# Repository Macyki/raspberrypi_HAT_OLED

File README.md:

# raspberrypi_HAT_OLED
# raspberrypi_HAT_OLED
# raspberrypi_HAT_OLED
# raspberrypi_HAT_OLED

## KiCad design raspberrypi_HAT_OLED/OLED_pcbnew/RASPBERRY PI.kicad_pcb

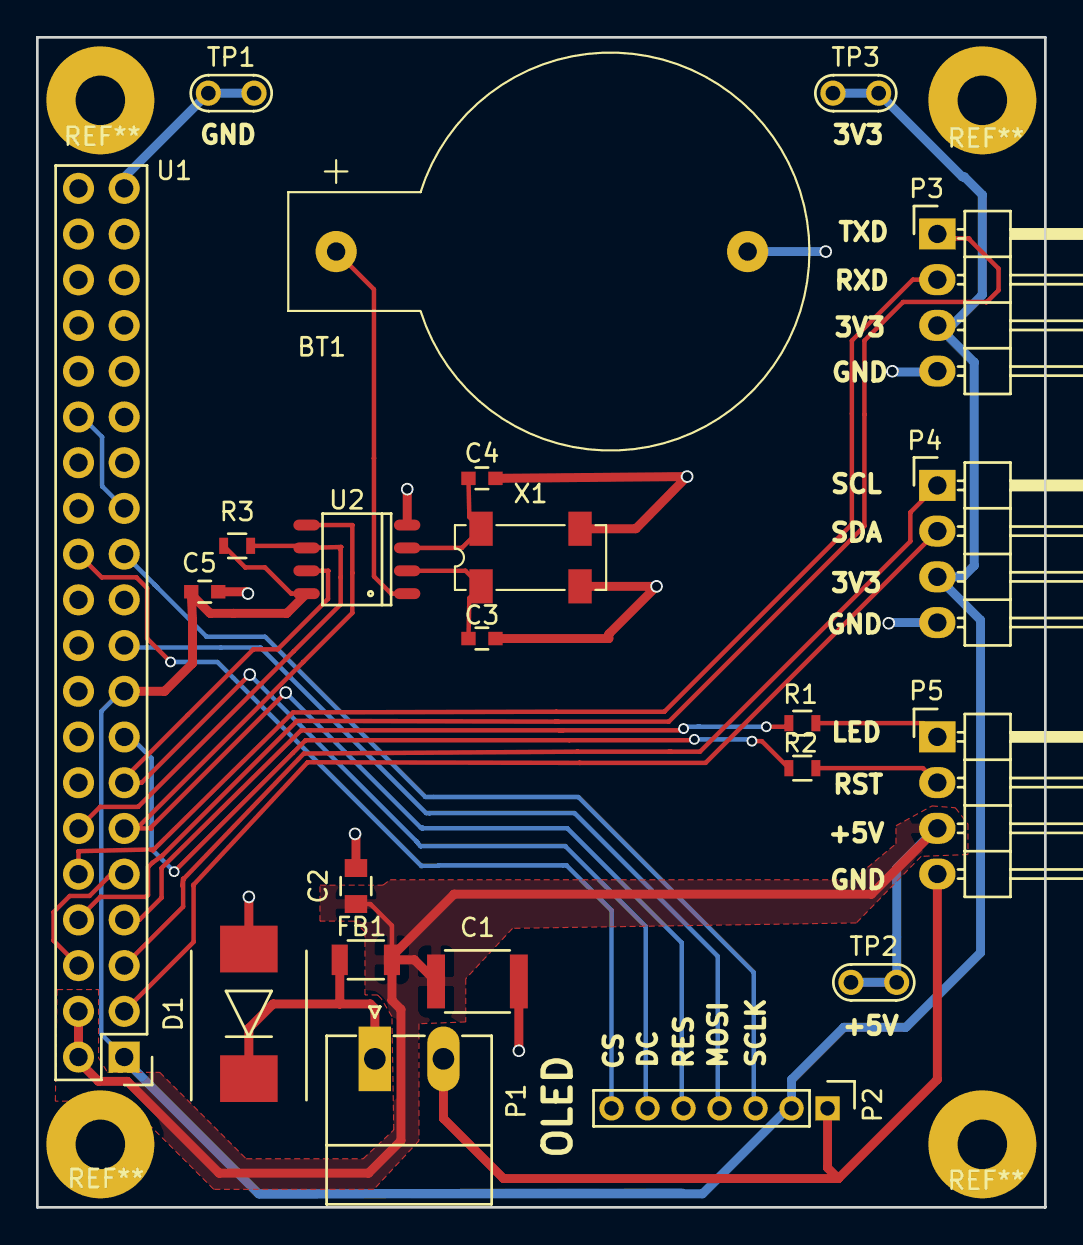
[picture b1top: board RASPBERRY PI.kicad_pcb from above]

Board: 2 copper layers, 56.0 x 65.0 mm, 22 parts (0 on the bottom side), 21 nets.

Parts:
BT1: CR1220-3V; CR2032H
C1: 47uF/10V/TAN; C_1812
C2: 2.2uF; C_0805
C3, C4: 10pF; C_0603
C5: 0.1uF; C_0603
D1: SAA5.0; DO-214AB
FB1: CIZHU_121R/6A; R_1206
P1: XH3.81-2P; PhoenixContact_MC-G_02x3.81mm_Angled
P2: XH2.0-7P; Pin_Header_Straight_1x07_Pitch2.00mm
P3, P4, P5: XH2.54-4P; Pin_Header_Angled_1x04
R1, R2: 330; R_0603
R3: 10K; R_0603
TP1, TP2, TP3: TESTPOINT; Test_Point
U1: Raspberry_Pi_B+; Pin_Header_Straight_2x20
U2: DS1302; SO-8
X1: E1WSDA12-32.768KHZ; Crystal_SMD_SeikoEpson_MC306-4pin_8.0x3.2mm

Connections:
+3V3: C5.1, P2.2, P3.3, P4.3, R3.1, TP3.1, U1.1, U1.17, U2.8
+5V: C1.1, C2.1, FB1.2, P5.3, TP2.1, U1.2, U1.4
/RTC_CE: P2.5, U1.11, U2.5
/RTC_IO: R3.2, U1.12, U2.6
/RTC_SCLK: P2.6, U1.13, U2.7
/SPI_CS: P2.7, U1.24
/SPI_MOSI: P2.4, U1.19
/SPI_SCLK: P2.3, U1.23
GND: BT1.2, C1.2, C2.2, C3.2, C4.2, C5.2, D1.2, P1.2, P2.1, P3.4, P4.4, P5.4, TP1.1, U1.6, U1.9, U1.14, U1.20, U1.25, U1.30, U1.34, U1.39, U2.4, X1.2, X1.3
unnamed: BT1.1, U2.1
unnamed: C3.1, U2.2, X1.1
unnamed: C4.1, U2.3, X1.4
unnamed: D1.1, FB1.1, P1.1
unnamed: P5.1, R1.1
unnamed: P5.2, R2.1
PIN_7: R1.2, U1.7
PIN_15: R2.2, U1.15
RXD: P3.2, U1.10
SCL: P4.1, U1.5
SDA: P4.2, U1.3
TXD: P3.1, U1.8
